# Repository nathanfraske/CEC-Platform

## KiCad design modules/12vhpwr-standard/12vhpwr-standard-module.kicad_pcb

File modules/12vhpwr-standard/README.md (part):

# 12VHPWR Standard module

Standard-tier **per-pin** sensing module for the **12VHPWR / 12V‑2×6** (PCIe CEM
5.x, 600 W GPU) connector. BOM target **$49** (100-qty). See spec
[§6.1](../../CEC-Platform-Ground-Truth-Spec.md).

Per CLAUDE.md's 2026-07-03 alpha/beta convention: this board is the **ALPHA**
line (validated, fab-snapshotted prototype); refinements land as **BETA**
revisions per the standard-tier beta plan
(`docs/standard-tier-review/SYNTHESIS-beta-plan.md`).

| Item | Decision |
|---|---|
| Tier | Standard |
| MCU | ESP32-S3-MINI-1-N4R2 (locked; same MINI-1 as the other modules) |
| Hub link | RJ-45 8P8C **shielded FTP**, locking boot (J1) — Kinghelm **KH-RJ45-58-8P8C** (LCSC **C2683360**), the same already-sourced jack as the Hub (§2.1; 2026-06-06). Drop-in on the routed 1.27 mm land (pads 1–8 identical to the old 54602). |
| Power connector | **12V‑2×6** (Molex Micro‑Fit+ / Amphenol Minitek, 16‑ckt: 6×+12V, 6×GND, 4 sideband). **J3 = board-mount right‑angle MALE header** (the PSU 12V‑2×6 cable plugs in). **J4 = captive OUTPUT pigtail** (a 12V‑2×6 cable soldered to the board, female plug → GPU). There is **no stock board‑mount female** 12V‑2×6 (it only exists as a cable plug), so this male‑in / soldered‑pigtail‑out is the minimal‑mated‑pair inline form (§2.8). |
| Sensing | **Per-pin**: six **INA240** current-sense amps, one across each +12V pin's **1 mΩ** shunt (RS1–6), feeding the ESP32-S3 ADC (IO1–6) directly — **no I²C sensing bus**. REF1/REF2 → GND (unidirectional forward). A **47k/10k divider** (R5/R6, **0.1%**) brings the rail voltage into a 7th ADC channel. With the **REF3030 ratiometric reference** (U4, v3.8) accuracy is **~±0.3–0.5%** on V and all six I (see **OQ-8** + the Voltage-ref row). |
| Input filter | Per-channel **anti-alias / transient RC** on each INA240 input: matched **10 Ω** series Rf on IN+/IN− (RFH1–6 / RFL1–6) + a **470 nF** differential cap (CF1–6). **fc = 1/(2π·2·Rf·Cdiff) ≈ 16.9 kHz**, so the ~10 kHz GPU transients this pass targets pass at ~−1.3 dB and HF is rolled off ahead of the ADC. Rf held at 10 Ω + matched (TI's INA240 ceiling) → negligible gain/CMRR error. *(Optional ~47 nF common-mode caps deferred — OQ-8.)* |
| Sideband | The four **12V-2×6 sense pins** (13–16: SENSE0, SENSE1, CARD_PWR_STABLE, CARD_CBL_PRES#) pass straight through J3→J4 **and** each taps a free ESP32-S3 GPIO (IO8/9/11/12) via a **1 kΩ** series R (R10–R13), so firmware can read the cable's advertised power capability + present/stable state and report it over CAN. |
| Temperature *(v3.7)* | **2× NTC 10k** (Murata **NCP15XH103F03RC** / LCSC **C77131**, 0402) into spare ESP32-S3 **ADC2** channels (this module never uses Wi-Fi, so ADC2 is free): **TH1** in the **12V power section by the shunt row** (board/shunt temperature), **TH2** ambient at a cool edge. Each is an NTC / 10 kΩ (R20/R21) / 100 nF (C20/C21) divider → **IO13 / IO14**; firmware reports temperature and **ΔT above ambient**. Purpose is **measurement quality + board health**: compensate the shunt-TCR / INA240-gain drift on the per-pin current readings, and flag 12V-section overheating — then board temp + per-pin current + rail voltage **fuse** to infer the off-board GPU-side condition. **Board-only**; a pigtail/GPU-plug NTC (the direct GPU-contact read) is **deferred**. Spec [§6.1](../../CEC-Platform-Ground-Truth-Spec.md). |
| Voltage ref *(v3.8)* | **REF3030** (U4, 3.0 V, SOT-23) measured on **ADC1 IO8** for **ratiometric correction** — firmware ratios out the ESP-ADC gain/reference drift, lifting the rail divider **and** all six current channels from ~±1% to **~±0.3–0.5%** (with **0.1%** R5/R6). Bypass C22 (OUT) + C23 (IN). The deliberate **middle ground** below the Pro's LTC2358-18; the REF3030 (3.0 V) is *measured* by the ADC, unlike the Pro's REF3033 (3.3 V) which feeds the LTC2358 ref. IO8 was freed by moving the SENSE0 sideband tap → **IO15**. See **OQ-8**. |
| Streaming | RS-485 **not populated** (Standard); pair 2 terminated module-side |
| DETECT | 2.2 kΩ precision (R1) — CAN-only code (§2.3, OQ-6 resolved); poke-and-ack tap R7 → IO10 (OQ-28) |
| Protection | No per-pin PoE/over-voltage (Standard/Pro, §2.4 v2.0); low-cap ESD diode **D1 = PESD5V0S1BA** (SOD-323, LCSC **C5261083**) on DETECT pin 8 — corrected from the non-SOD-323 PESD5V0S1UL on the 2026-06-06 sourcing pass |
| Flash/debug | USB-C (J5) on the ESP32-S3 native USB + BOOT/RESET buttons (SW1/SW2); VBUS ORs into +5VSB via D2 (SS34); CC1/CC2 = 5.1 kΩ |
| BOM target | $49 (100-qty) |

> ✅ **12V‑2×6 footprint LOCKED (2026-06-05).** `lib/cec.pretty/CEC_12V2x6_Horizontal`
> is now the **official Molex footprint** — Molex **219116** PCIe CEM5 12V‑2×6
> right‑angle THT header, MPN **2191161161** (T&R) = **2191160161** (tray), doc
> 2191160001‑SD — vendored from Molex's KiCad export, pads remapped to the schematic
> numbering: **1–6 = +12V** (row adjacent to the signal pins), **7–12 = GND** (outer
> row), **13–16 = sideband S1–S4**. Real geometry: 3 mm pitch, power drill 1.07 mm /
> 1.52 mm pad, signal drill 0.61 mm / 1.14 mm pad; **9.2 A/power pin**, 12 V.
>
> Two follow‑ups: **(1) safety —** the connector is symmetric (both rows are just
> "POWER"); +12V vs GND is the system/CEM assignment, so **verify pins 7–12 = GND**
> (i.e. 1–6 = +12V) against PCIe CEM5.1 / the target GPU before powering, since the
> schematic ties 7–12 to the GND plane. **(2) board pickup —** the board still
> carries the old approximate land; in KiCad do **Update Footprints from Library**
> to pull this one (converts + remaps nets by pad number), then orient **J3 rot 180
> / J4 rot 0** (this footprint's mouth is on +y, so that puts the mouth out the edge
> with GND toward the shunts). The real ~1.5 mm pad gaps let the +12V lanes neck
> between the GND barrels (vs the old ~0.6 mm approximate that trapped them).

## Open questions touching this board

- **OQ-8 (RESOLVED, v3.8 — revises the v3.7 no-ref call):** rail accuracy — a
  **REF3030** (3.0 V) ratiometric reference (U4), measured by the ESP ADC1, lifts
  the rail divider **and** all six current channels from ~±1% to **~±0.3–0.5%**
  (0.1% R5/R6) — the **middle ground** between the bare divider and the Pro's
  precision instrument. It's the *reference*, not a second ADC or a sensing bus, so
  Standard stays the fast firehose, just accurate + stable (stability is what makes
  a connector-degradation / dV·dI source-impedance trend real). Full simultaneous
  precision stays the Pro (LTC2358-18 + REF3033). Note: Standard REF3030 = 3.0 V
  (*measured* by the ADC); Pro REF3033 = 3.3 V (feeds the LTC2358 ref).
- *(OQ-11 resolved 2026-07-02 — per-pin shunt part (1 mΩ, §6.4) LOCKED to Bourns
  CSS2H-2512R-1L00F, already the sourced part on this board.)*
- *(OQ-6 module-ID encoding resolved — CAN-only = 2.2 kΩ.)*

## High-current 12V routing — fanned per-pin lanes

See **`12vhpwr-routing-plan.png`** (regenerate with
`scripts/gen-hpwr-routing-plan.py`) — it carries the full to-placement top-down,
the four-wire Kelvin detail, the 4-layer stackup, and the width/via/stitch tables.
The 6×+12V pins carry ~**8.3 A each** (600 W ÷ 12 V = 50 A); **uneven sharing is
what melts these connectors**, so the module gives each pin its own 1 mΩ shunt +
INA240 and keeps the six 12V lanes symmetric so it adds no imbalance (and detects
any). Routing spec (laid in the GUI — the generator only sets placement):

- **Lanes / fan-out:** J3 and J4 are 12V‑2×6 connectors with a fixed **3 mm pin
  pitch**, centered on the power section; the six +12V lanes **fan out symmetrically
  to a ~6 mm SENSE pitch**, so each lane gets its OWN column — in-line shunt → RC
  filter → INA240 stacked straight down (no staggering, short in-column Kelvin) —
  then **fan back in** to J4. **J4 is placed rot 180°** (mouth out the bottom edge =
  correct OUT orientation, mirroring J3 at the top); since the six +12V pins are
  electrically interchangeable (all common to the GPU 12V plane, current already
  measured at each shunt upstream), each lane's load side is mapped to the J4 +12V
  pad directly below it (pin 6−*j*) so the lanes still **don't cross** despite the
  180. The symmetric fan keeps the lanes in equal-length pairs; if the small inner/outer
  length spread matters, length-match the straight section in the GUI (the 1 mΩ
  shunt + connector-contact R dominate, so it's minor).
- **Width (IPC-2221, 2 oz outer):** design to the **contact** rating, not nominal —
  Micro-Fit+ ≈ 9.5–13.5 A/contact → **13 A/pin**. Route each lane **2.5 mm on F.Cu,
  mirrored 2.5 mm on B.Cu, paralleled** (≈13 A at <10 °C rise; ≥3.0 mm if a B.Cu
  mirror is interrupted). **12V on both 2 oz outers; GND solid on In1 + In2** (1 oz,
  set BOTH inner pours to GND). Stack is **12V / GND / GND / 12V**, so it's the GND
  pair that sits in the middle (sandwiched by the two 12V outers); each 12V lane
  runs **directly against a GND plane** (F.Cu over In1, B.Cu under In2) → its return
  image-current flows in that plane right beneath the lane → small loop area, low
  inductance. GND return = poured plane (never neck it).
- **Vias:** all current-carrying vias **0.5 mm drill / 0.9 mm pad (~2 A @10 °C,
  ~3 A @20 °C)**. Stitch F.Cu↔B.Cu **every ~5 mm down each lane**, with a **field of
  5–6** at every shunt terminal and **3–6 around each J3/J4 through-hole power pin**.
  Tie In1/In2/outer-GND on a **~5 mm grid** (denser ~3 mm ring at the connectors).
  Signal/sense vias 0.3/0.6 mm (~1 A) — avoid them on the Kelvin pair.
- **Kelvin sense (§6.8):** INA240A3 (gain 100) → 1 mΩ × 8.3 A × 100 = 0.83 V
  (13 A → 1.3 V). **Sense taps off the INNER shunt-terminal edges** (excludes pad/
  solder/trace IR drop); force current on the OUTER ends. The pair carries ~no
  current → run it **thin (0.20–0.25 mm)** as a **tight matched-length pair over the
  In1 GND plane**, kept off / perpendicular to the 12V lanes, with the RC input
  filter (RFH/RFL 10 Ω + CF 470 nF) placed **at the INA pins**. A GND guard-via
  fence alongside the pair is cheap insurance (the 12V here is essentially DC, so
  coupling is low, but the signal is only 8–13 mV).

## Status

Schematic generated by `scripts/gen-modules.py`; the initial PCB floorplan by
`scripts/gen-module-pcb.py` (one-shot — hand-maintained in the GUI afterwards):
4-layer, **2 oz outer / 1 oz inner**, **~58 × 80 mm** — the 12V‑2×6 power path runs
TOP→BOTTOM down the centre-left (J3 IN top → 6 **fanned** per-pin lanes, each with
its in-line shunt → RC filter → INA240 → bypass → J4 pigtail OUT bottom); the
ESP + CAN + LDO + flash front end + RJ-45/USB-C fill the RIGHT. The six +12V lanes
**fan out from J3/J4's 3 mm pin pitch to a ~6 mm sense pitch** so each lane gets its
own column (in-column shunt/filter/INA, short Kelvin, no staggering). The **plug
connectors overhang their board edge** so a cable seats without the board fouling
the plug overmold while the solder pads stay on-board: **J3** (PSU 12V‑2×6 IN, top-
centre) overhangs the **top** edge ~3 mm; **J1** (RJ-45) and **J5** (USB-C) overhang
the **right** edge. **J4** (12V‑2×6 OUT) is **rot 180°** so its mouth/body overhang
the **bottom** edge too (correct OUT orientation, mirroring J3); the +12V load nets
are remapped to the reversed pins (pin 6−*j*, interchangeable) so the lanes stay
non-crossing. It's a captive soldered pigtail (wires exit the bottom). **Three M3 corner mounts**
(TL/TR/BL) — the RJ-45's big jack body fills the bottom-right corner, and the three
through-hole connectors anchor that side. The **per-lane sense passives are now
placed** (RFH/RFL/CF input filter + the INA bypass C10–C15); **component values are
on F.SilkS**. **DRAFT** marker present; DRC is **clean of structural hits** (0 copper
shorts / clearance / courtyard / copper-edge) — the remaining silk-overlap warnings
are the dense values-on-silk + tight placement, a GUI silk-refinement task. Next in
GUI: *Update PCB from Schematic* to pull the remaining **control-side decoupling**
(C1–C8, R1/R2/R7, D1), then route + pour (§6.8 Kelvin, §6.7 high-current).
Project-local library tables point at `../../lib` via `${KIPRJMOD}`.

## Routing status (2026-06-05)

**Part audit — all clear.** Every vendored symbol used on this board (and in the
shared lib) had its pin#→name mapping checked against the manufacturer datasheet:
INA240 (1=IN−, 2=GND, 3=REF2, 4=NC → tied to GND, which the datasheet sanctions,
5=OUT, 6=V+, 7=REF1, 8=IN+), INA226/228/238 (identical DGS VSSOP‑10), TJA1051T/3,
LP5907, ESP32‑S3‑MINI‑1, RJ‑45, USB‑C, the 12V‑2×6, and the rest — **all correct,
no mis‑wires.** (Cosmetic‑only notes are in the repo CLAUDE.md.)

**High‑current path — DONE.** All six +12V lanes carry end‑to‑end: J3 +12V → shunt
on **F.Cu** (2.5 mm, fanned 3→6 mm), shunt → J4 +12V on **B.Cu** (2.5 mm). Lane 3's
full sense chain is routed as the reference.

**Remaining — 47 ratlines, all sense/signal** (see **`12vhpwr-route-plan.png`**,
regenerate with `scripts/gen-hpwr-route-status.py`):
- All six **INA OUT → ESP ADC IO1–6** (ISENSEP1–6).
- **Kelvin taps** off the inner shunt‑terminal edges → RFH/RFL, and **RC filter →
  INA IN+/IN−**, on lanes 1, 2, 4, 5, 6 (route them like the finished lane 3):
  0.25 mm matched pair over the In1 GND plane, ⊥ to the 12V lanes, filter at the INA.

**Before re‑checking DRC** (current DRC = 47 unconnected + 291 violations):
- **Fill All Zones (B).** 252 of the violations are `clearance`/`hole_clearance`
  reading *actual 0.000 mm* — that is **stale GND‑pour** (kicad‑cli cannot refill),
  not real shorts. Set **both** inner zones to GND.
- Delete **18 dangling vias + 3 dangling track stubs**.
- **Update PCB from Schematic** — syncs U2 value (the PCB still shows the old
  *TJA1462A*; the schematic is already *TJA1051T/3*, C38695; footprint identical).
- **Outline fixed:** the Molex 12V‑2×6 footprint's mouth/latch profile was on
  Edge.Cuts (read as a malformed board outline); moved to Dwgs.User in the library
  and in J3/J4 (invalid_outline 4→0).

**Note — J4 orientation:** with the official Molex footprint J4 is **rot 0°** (mouth
out the bottom edge) and J3 is **rot 180°** (mouth out the top); this supersedes the
"J4 rot 180°" wording in the Status paragraph above.

## BOM / JLC sourcing (2026-06-06)

Every component is sourced to an LCSC part (written into the schematic symbol
`LCSC`/`MPN`/`Manufacturer` props) and exported in `bom/`:
`bom.csv` (tracking) + `12vhpwr-standard-BOM-jlcpcb.csv` (Comment/Designator/Footprint/LCSC).
**~$21/board** in JLCPCB parts (single-qty pricing) + the consigned Molex 12V‑2×6 —
comfortably under the **$49** target; cost is dominated by **6× INA240A3DR ($1.87 ea =
$11.24)**, the **ESP32 ($4.59)**, and the **6× 1 mΩ shunts ($0.52 ea)**.

Pinouts datasheet-verified this pass (INA240 SBOS662C, LP5907 SNVS798Q, ESP32‑S3‑MINI‑1
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
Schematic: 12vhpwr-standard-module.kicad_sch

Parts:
C1, C2: 1uF; C_0603_1608Metric; MPN CL10B105KA8NNNC; LCSC C29936
C3, C4, C5, C8, C10, C11, C12, C13, C14, C15, C20, C21, C22, C23: 100nF; C_0402_1005Metric; MPN CL05B104KO5NNNC; LCSC C1525
C6, C7, C9: 10uF; C_0805_2012Metric; MPN CL21A106KAYNNNE; LCSC C15850
C24: 1nF; C_0402_1005Metric; MPN GRM1555C1H102JA01D; LCSC C76947
CF1, CF2, CF3, CF4, CF5, CF6: 470nF; C_0603_1608Metric; MPN CL10B474KA8NNNC; LCSC C1623
D1: PESD5V0S1BA; D_SOD-323; MPN PESD5V0S1BA; LCSC C5261083
D2: SS34; D_SMA; MPN SS34; LCSC C8678
J1: TO-HUB; RJ45_FTP_Shielded_Horizontal; MPN KH-RJ45-58-8P8C; LCSC C2683360
J3: 12V-2x6 IN; CEC_12V2x6_Horizontal; MPN 2191161161; JLCPCB consigned (not in JLC catalog)
J4: 12V-2x6 OUT pigtail; CEC_12V2x6_Horizontal; MPN 2191161161; JLCPCB consigned (not in JLC catalog)
J5: USB-C 2.0; USB_C_Receptacle_XKB_U262-16XN-4BVC11; MPN U262-161N-4BVC11; LCSC C319148
R1: 2.2kΩ; R_0402_1005Metric; MPN 0402WGF2201TCE; LCSC C25879
R2, R20, R21: 10kΩ; R_0402_1005Metric; MPN 0402WGF1002TCE; LCSC C25744
R5: 47kΩ; R_0402_1005Metric; Tolerance 0.1%; MPN RT0402BRD0747KL; LCSC C728561
R6: 10kΩ; R_0402_1005Metric; Tolerance 0.1%; MPN RT0402BRD0710KL; LCSC C190095
R7: 100kΩ; R_0402_1005Metric; MPN 0402WGF1003TCE; LCSC C25741
R8, R9: 5.1kΩ; R_0402_1005Metric; MPN 0402WGF5101TCE; LCSC C25905
R10, R11, R12, R13: 1kΩ; R_0402_1005Metric; MPN 0402WGF1001TCE; LCSC C11702
RFH1, RFH2, RFH3, RFH4, RFH5, RFH6: 10Ω; R_0402_1005Metric; Tolerance 0.1%; MPN RT0402BRE0710RL; LCSC C705642
RFL1, RFL2, RFL3, RFL4, RFL5, RFL6: 10Ω; R_0402_1005Metric; Tolerance 0.1%; MPN RT0402BRE0710RL; LCSC C705642
RS1, RS2, RS3, RS4, RS5, RS6: 1mΩ; R_2512_6332Metric; MPN CSS2H-2512R-1L00F; LCSC C4175647
SW1: BOOT; TS-1088-AR02016; MPN TS-1088-AR02016; LCSC C720477
SW2: RESET; TS-1088-AR02016; MPN TS-1088-AR02016; LCSC C720477
TH1, TH2: NTC 10k; NTC_0402_1005Metric; MPN NCP15XH103F03RC; LCSC C77131
U1: ESP32-S3-MINI-1-N4R2; ESP32-S2-MINI-1_NoAntKeepout; MPN ESP32-S3-MINI-1-N4R2; LCSC C3013941
U2: TJA1051T/3; SOIC-8_3.9x4.9mm_P1.27mm; MPN TJA1051T/3; LCSC C38695
U3: LP5907MFX-3.3; SOT-23-5; MPN LP5907MFX-3.3; LCSC C80670
U4: REF3030; REF3030_DBZ3; MPN REF3030AIDBZR; LCSC C38423
U10, U11, U12, U13, U14, U15: INA240A3; SOIC-8_3.9x4.9mm_P1.27mm; MPN INA240A3DR; LCSC C2060584

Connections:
+3V3: C2.1, C3.1, C7.1, C8.1, C10.1, C11.1, C12.1, C13.1, C14.1, C15.1, C23.1, R2.1, TH1.1, TH2.1, U1.3 (3V3), U2.5 (VIO), U3.5 (OUT), U4.1 (IN), U10.6 (V+), U11.6 (V+), U12.6 (V+), U13.6 (V+), U14.6 (V+), U15.6 (V+)
+5VSB: C1.1, C4.1, C6.1, D2.1 (K), J1.1 (VCC), U2.3 (VCC), U3.1 (IN), U3.3 (EN)
/CAN_H: J1.3 (CAN1_H), U2.7 (CANH)
/CAN_L: J1.6 (CAN1_L), U2.6 (CANL)
/CAN_RX: U1.22 (IO18), U2.4 (RXD)
/CAN_TX: U1.21 (IO17), U2.1 (TXD)
/DETECT: D1.1 (K), J1.8 (DETECT), R1.1, R7.1
/DETECT_SENSE: R7.2, U1.14 (IO10)
/EN: C5.1, R2.2, SW2.2, U1.45 (EN)
/GPIO0: SW1.2, U1.4 (IO0)
/IN1_N: CF1.2, RFL1.2, U10.1 (-)
/IN1_P: CF1.1, RFH1.2, U10.8 (+)
/IN2_N: CF2.2, RFL2.2, U11.1 (-)
/IN2_P: CF2.1, RFH2.2, U11.8 (+)
/IN3_N: CF3.2, RFL3.2, U12.1 (-)
/IN3_P: CF3.1, RFH3.2, U12.8 (+)
/IN4_N: CF4.2, RFL4.2, U13.1 (-)
/IN4_P: CF4.1, RFH4.2, U13.8 (+)
/IN5_N: CF5.2, RFL5.2, U14.1 (-)
/IN5_P: CF5.1, RFH5.2, U14.8 (+)
/IN6_N: CF6.2, RFL6.2, U15.1 (-)
/IN6_P: CF6.1, RFH6.2, U15.8 (+)
/ISENSEP1: U1.5 (IO1), U10.5
/ISENSEP2: U1.6 (IO2), U11.5
/ISENSEP3: U1.7 (IO3), U12.5
/ISENSEP4: U1.8 (IO4), U13.5
/ISENSEP5: U1.9 (IO5), U14.5
/ISENSEP6: U1.10 (IO6), U15.5
/SB_CBL_PRES: J3.16 (SENSE), J4.16 (SENSE), R13.1
/SB_CBL_PRES_GPIO: R13.2, U1.16 (IO12)
/SB_PWR_STABLE: J3.15 (SENSE), J4.15 (SENSE), R12.1
/SB_PWR_STABLE_GPIO: R12.2, U1.15 (IO11)
/SB_SENSE0: J3.13 (SENSE), J4.13 (SENSE), R10.1
/SB_SENSE0_GPIO: R10.2, U1.19 (IO15)
/SB_SENSE1: J3.14 (SENSE), J4.14 (SENSE), R11.1
/SB_SENSE1_GPIO: R11.2, U1.13 (IO9)
/SENSEP1_HI: J3.1 (+12V), RFH1.1, RS1.1
/SENSEP1_LO: J4.6 (+12V), RFL1.1, RS1.2
/SENSEP2_HI: J3.2 (+12V), RFH2.1, RS2.1
/SENSEP2_LO: J4.5 (+12V), RFL2.1, RS2.2
/SENSEP3_HI: J3.3 (+12V), RFH3.1, RS3.1
/SENSEP3_LO: J4.4 (+12V), RFL3.1, RS3.2
/SENSEP4_HI: J3.4 (+12V), RFH4.1, RS4.1
/SENSEP4_LO: J4.3 (+12V), RFL4.1, RS4.2
/SENSEP5_HI: J3.5 (+12V), RFH5.1, RS5.1
/SENSEP5_LO: J4.2 (+12V), RFL5.1, RS5.2
/SENSEP6_HI: J3.6 (+12V), R5.1, RFH6.1, RS6.1
/SENSEP6_LO: J4.1 (+12V), RFL6.1, RS6.2
/TEMP1: C20.1, R20.1, TH1.2, U1.17 (IO13)
/TEMP2: C21.1, R21.1, TH2.2, U1.18 (IO14)
/USB_CC1: J5.A5 (CC1), R8.1
/USB_CC2: J5.B5 (CC2), R9.1
/USB_DM: J5.A7 (D-), J5.B7 (D-), U1.23 (USB_D-)
/USB_DP: J5.A6 (D+), J5.B6 (D+), U1.24 (USB_D+)
/VBUS: C9.1, D2.2 (A), J5.A4 (VBUS), J5.A9 (VBUS), J5.B4 (VBUS), J5.B9 (VBUS)
/VRAIL_DIV: C24.1, R5.2, R6.1, U1.11 (IO7)
/VREF: C22.1, U1.12 (IO8), U4.2 (OUT)
GND: C1.2, C2.2, C3.2, C4.2, C5.2, C6.2, C7.2, C8.2, C9.2, C10.2, C11.2, C12.2, C13.2, C14.2, C15.2, C20.2, C21.2, C22.2, C23.2, C24.2, D1.2 (A), J1.2 (GND), J1.SH1 (SHIELD), J1.SH2 (SHIELD), J3.7 (GND), J3.8 (GND), J3.9 (GND), J3.10 (GND), J3.11 (GND), J3.12 (GND), J4.7 (GND), J4.8 (GND), J4.9 (GND), J4.10 (GND), J4.11 (GND), J4.12 (GND), J5.A1 (GND), J5.A12 (GND), J5.B1 (GND), J5.B12 (GND), J5.S1 (SHIELD), R1.2, R6.2, R8.2, R9.2, R20.2, R21.2, SW1.1, SW2.1, U1.1 (GND), U1.2 (GND), U1.42 (GND), U1.43 (GND), U1.46 (GND), U1.47 (GND), U1.48 (GND), U1.49 (GND), U1.50 (GND), U1.51 (GND), U1.52 (GND), U1.53 (GND), U1.54 (GND), U1.55 (GND), U1.56 (GND), U1.57 (GND), U1.58 (GND), U1.59 (GND), U1.60 (GND), U1.61 (GND), U1.62 (GND), U1.63 (GND), U1.64 (GND), U1.65 (GND), U2.2 (GND), U2.8 (S), U3.2 (GND), U4.3 (GND), U10.2 (GND), U10.3 (REF2), U10.4 (GND), U10.7 (REF1), U11.2 (GND), U11.3 (REF2), U11.4 (GND), U11.7 (REF1), U12.2 (GND), U12.3 (REF2), U12.4 (GND), U12.7 (REF1), U13.2 (GND), U13.3 (REF2), U13.4 (GND), U13.7 (REF1), U14.2 (GND), U14.3 (REF2), U14.4 (GND), U14.7 (REF1), U15.2 (GND), U15.3 (REF2), U15.4 (GND), U15.7 (REF1); also elsewhere on the board

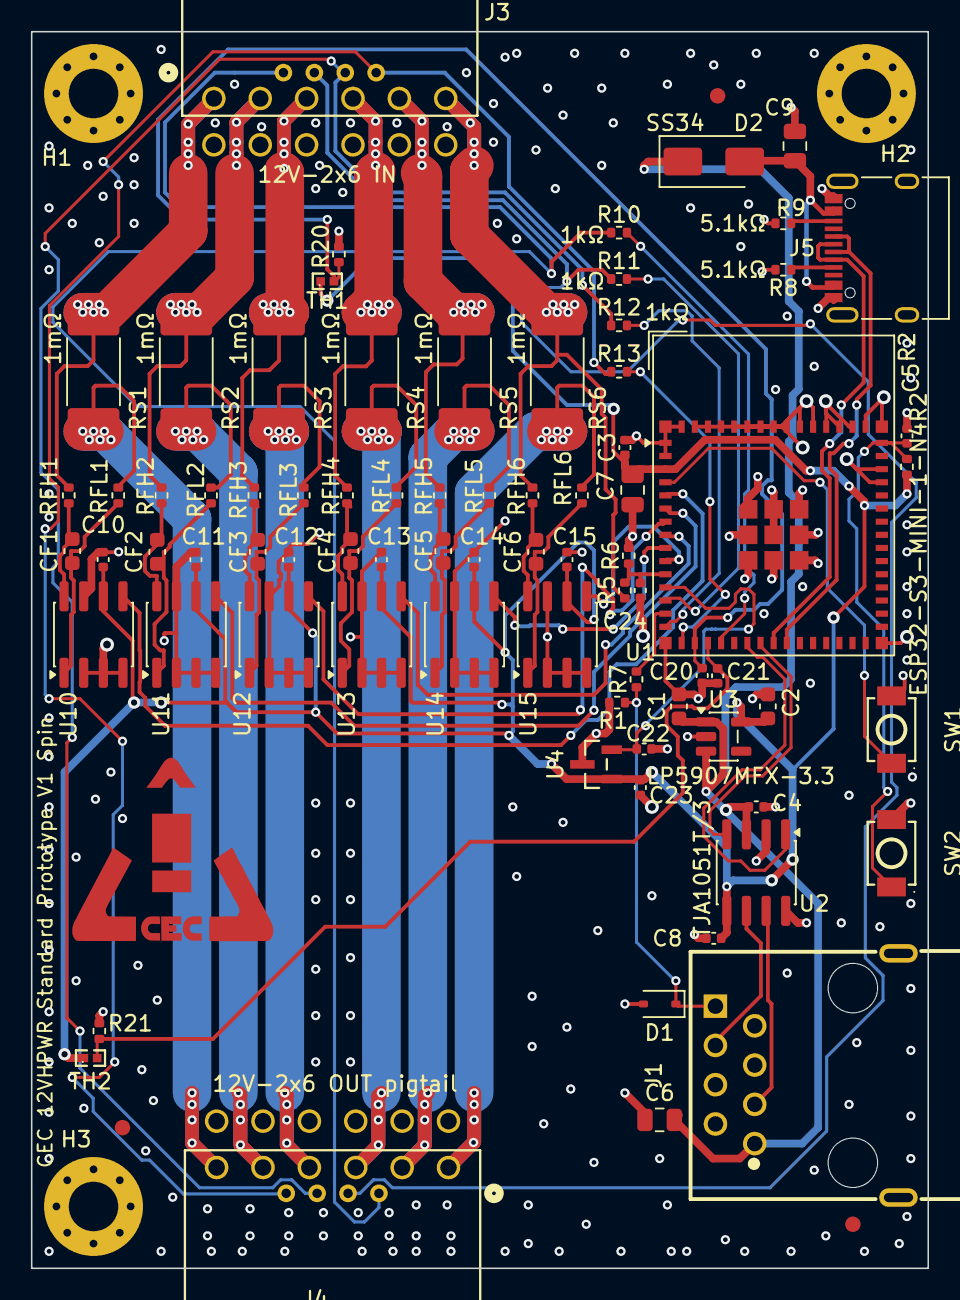
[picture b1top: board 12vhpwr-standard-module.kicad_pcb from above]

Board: 4 copper layers, 58.0 x 80.0 mm, 84 parts (0 on the bottom side), 58 nets.

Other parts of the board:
FID1, FID2, FID3: Fiducial_1mm_Mask2mm
H1, H2, H3: MountingHole_3.2mm_M3_Pad_Via
LOGO1: CEC_Logo_Copper

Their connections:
GND: H1.1, H2.1, H3.1; also elsewhere on the board

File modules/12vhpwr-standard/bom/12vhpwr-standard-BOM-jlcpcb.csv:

Comment,Designator,Footprint,LCSC
1uF,"C1,C2",C_0603_1608Metric,C29936
100nF,"C3,C4,C5,C8,C10,C11,C12,C13,C14,C15,C20,C21,C22,C23",C_0402_1005Metric,C1525
10uF,"C6,C7,C9",C_0805_2012Metric,C15850
1nF,C24,C_0402_1005Metric,C76947
470nF,"CF1,CF2,CF3,CF4,CF5,CF6",C_0603_1608Metric,C1623
PESD5V0S1BA,D1,D_SOD-323,C5261083
SS34,D2,D_SMA,C8678
TO-HUB,J1,RJ45_FTP_Shielded_Horizontal,C2683360
12V-2x6 IN,J3,CEC_12V2x6_Horizontal,
12V-2x6 OUT pigtail,J4,CEC_12V2x6_Horizontal,
USB-C 2.0,J5,USB_C_Receptacle_XKB_U262-16XN-4BVC11,C319148
2.2kΩ,R1,R_0402_1005Metric,C25879
10kΩ,"R2,R20,R21",R_0402_1005Metric,C25744
47kΩ,R5,R_0402_1005Metric,C728561
10kΩ,R6,R_0402_1005Metric,C190095
100kΩ,R7,R_0402_1005Metric,C25741
5.1kΩ,"R8,R9",R_0402_1005Metric,C25905
1kΩ,"R10,R11,R12,R13",R_0402_1005Metric,C11702
10Ω,"RFH1,RFH2,RFH3,RFH4,RFH5,RFH6,RFL1,RFL2,RFL3,RFL4,RFL5,RFL6",R_0402_1005Metric,C705642
1mΩ,"RS1,RS2,RS3,RS4,RS5,RS6",R_2512_6332Metric,C4175647
BOOT,SW1,TS-1088-AR02016,C720477
RESET,SW2,TS-1088-AR02016,C720477
NTC 10k,"TH1,TH2",NTC_0402_1005Metric,C77131
ESP32-S3-MINI-1-N4R2,U1,ESP32-S2-MINI-1_NoAntKeepout,C3013941
TJA1051T/3,U2,SOIC-8_3.9x4.9mm_P1.27mm,C38695
LP5907MFX-3.3,U3,SOT-23-5,C80670
REF3030,U4,REF3030_DBZ3,C38423
INA240A3,"U10,U11,U12,U13,U14,U15",SOIC-8_3.9x4.9mm_P1.27mm,C2060584

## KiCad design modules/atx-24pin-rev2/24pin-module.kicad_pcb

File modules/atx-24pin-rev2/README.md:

# atx-24pin-rev2 — right-angle layout variant

Same circuit as [`../atx-24pin`](../atx-24pin) (the canonical 24-pin ATX
interposer); **different PCB layout only** — 24-pin input (J3) with the 24-pin
output (J4) rotated 90° CCW for a right-angle cable exit.

## Known issue (prototype run) — RJ-45 VCC parallels the JST feed

rev2 ties **J1 pin 1 (RJ-45 VCC)** to `+5VSB`, so the module feeds the Hub on
**both** the dedicated JST 5VSB feed **and** its RJ-45 VCC pin, in parallel.
Because the Hub power mux sits only in the JST leg (JST = mux input, RJ-45 VCC =
mux output), a **short RJ-45 patch** makes the RJ-45 the lower-resistance path —
it carries the majority of the bulk current (up to ~1.7 A at 3 A total, over the
**1.5 A RJ-45 contact rating**) and bypasses the mux's PSU/USB OR-ing. Fixed on
rev3 by leaving J1.1 open (spec §2.7 v3.3); rev2 is ordered as-is, so mitigate at
bring-up — any one of:

1. **Long RJ-45 patch (≥1.5–2 m)** on the 24-pin↔Hub link: the conductor
   resistance then exceeds the JST+mux path, so the JST carries the bulk. No mod.
2. **Keep total 5VSB low:** cap the firmware LED budget and don't run all ports
   full-white. Under ~2 A total, even a 50/50 split keeps the RJ-45 VCC well
   under 1.5 A.
3. **Bodge — open J1 pin 1:** lift the RJ-45 VCC pin or knife-cut its trace to
   `+5VSB`, emulating the rev3 fix. Most robust; do this if you'll push full
   load. The module still self-powers from its ATX tap.

Don't run a fully-populated, full-LED system through a short patch on an
un-bodged rev2.

## Shared schematic (canonical = atx-24pin)
The schematic here is a **synced copy**. The source of truth is
`../atx-24pin/24pin-module.kicad_sch`.

1. Edit the schematic in `../atx-24pin`.
2. Run `./sync-schematic.sh` here to refresh this copy.
3. **Tools → Update PCB from Schematic** in this project's board.

Do not edit this copy directly — `sync-schematic.sh` overwrites it from canonical.

## PCB
Starts as a blank slate: **only J3 and J4 are placed**, on the inherited 1 oz
stackup + netclasses (USB/CAN/Power/HighCurrent) + design rules. Everything else
arrives via *Update PCB from Schematic*, ready to place around the right-angle
header arrangement. (A fresh DRC will show unconnected items until that import.)

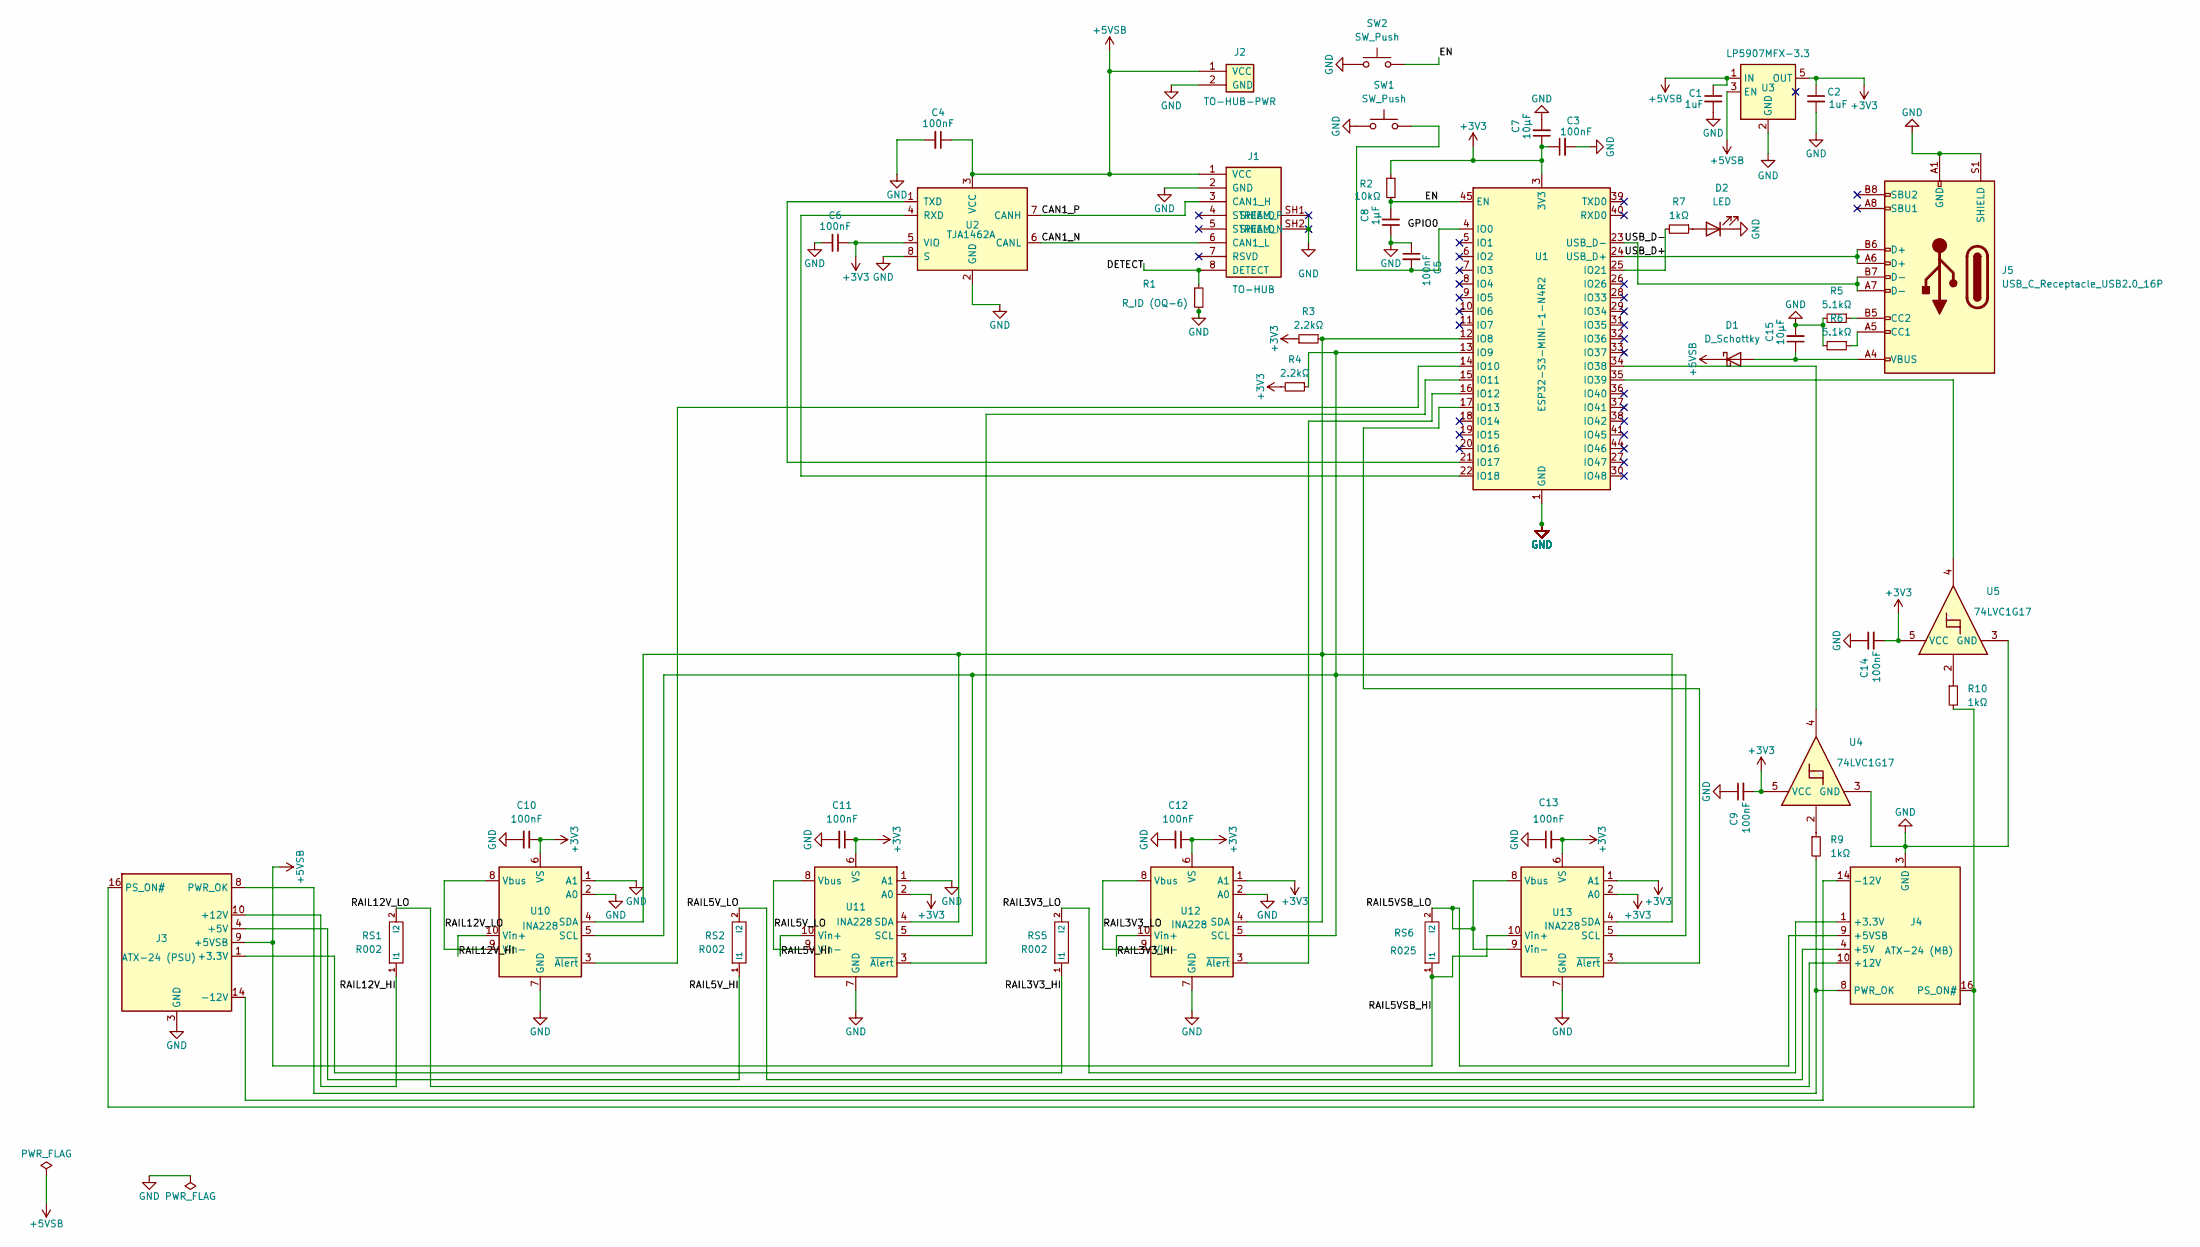
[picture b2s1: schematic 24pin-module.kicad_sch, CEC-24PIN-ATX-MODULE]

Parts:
C1, C2: 1uF; C_0603_1608Metric; Tolerance 10%; Voltage 25V
C3, C4, C5, C6, C10, C11, C12, C13: 100nF; C_0402_1005Metric; Tolerance 10%; Voltage 25V
C7, C15: 10µF; C_0805_2012Metric; Tolerance 10%; Voltage 25V
C8: 1µF; C_0805_2012Metric; Tolerance 10%; Voltage 25V
C9, C14: 100nF; C_0402_1005Metric; Voltage 25V; Tolerance 10%
D1: D_Schottky; D_SMA; MPN SS34; LCSC C8678
D2: LED; LED_0603_1608Metric
J1: TO-HUB; RJ45_Amphenol_54602-x08_Horizontal
J2: TO-HUB-PWR; JST_XH_S2B-XH-A_1x02_P2.50mm_Horizontal
J3: ATX-24 (PSU); Molex_Mini-Fit_Jr_5569-24A1_2x12_P4.20mm_Horizontal
J4: ATX-24 (MB); Molex_Mini-Fit_Jr_5569-24A1_2x12_P4.20mm_Horizontal
J5: USB_C_Receptacle_USB2.0_16P; USB_C_Receptacle_XKB_U262-16XN-4BVC11
R1: R_ID (OQ-6); R_0402_1005Metric; Tolerance 1%
R2: 10kΩ; R_0402_1005Metric; Tolerance 1%
R3, R4: 2.2kΩ; R_0402_1005Metric; Tolerance 1%
R5, R6: 5.1kΩ; R_0402_1005Metric; Tolerance 1%
R7, R9, R10: 1kΩ; R_0402_1005Metric; Tolerance 1%
RS1, RS2, RS5: R002; R_2512_6332Metric; Tolerance 1%; MPN CSS2H-2512K-2L00F; LCSC C1729157
RS6: R025; R_2512_6332Metric; Tolerance 1%
SW1, SW2: SW_Push; Panasonic_EVQPUJ_EVQPUA
U1: ESP32-S3-MINI-1-N4R2; ESP32-S2-MINI-1_NoAntKeepout; MPN ESP32-S3-MINI-1-N4R2; LCSC C3013941
U2: TJA1462A; SOIC-8_3.9x4.9mm_P1.27mm; MPN TJA1462AT/0Z; LCSC C3234095
U3: LP5907MFX-3.3; SOT-23-5; MPN LP5907MFX-3.3/NOPB; LCSC C80670
U4, U5: 74LVC1G17; SOT-23-5; MPN SN74LVC1G17DBVR; LCSC C7836
U10, U11, U12, U13: INA228; VSSOP-10_3x3mm_P0.5mm; MPN INA228AIDGSR; LCSC C2887910

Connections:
+3V3: C2.1, C3.1, C6.1, C7.1, C9.2, C10.1, C11.1, C12.1, C13.2, C14.2, R2.1, R3.1, R4.2, U1.3 (3V3), U2.5 (VIO), U3.5 (OUT), U4.5 (VCC), U5.5 (VCC), U10.6 (VS), U11.2 (A0), U11.6 (VS), U12.1 (A1), U12.6 (VS), U13.1 (A1), U13.2 (A0), U13.6 (VS)
+5VSB: C1.1, C4.1, D1.1 (K), J1.1 (VCC), J2.1 (VCC), J3.9 (+5VSB), RS6.1 (I1), U2.3 (VCC), U3.1 (IN), U3.3 (EN), U13.10 (Vin+)
/CAN1_N: J1.6 (CAN1_L), U2.6 (CANL)
/CAN1_P: J1.3 (CAN1_H), U2.7 (CANH)
/DETECT: J1.8 (DETECT), R1.1
/EN: C8.2, R2.2, SW2.2, U1.45 (EN)
/GPIO0: C5.2, SW1.2, U1.4 (IO0)
/RAIL3V3_HI: J3.1 (+3.3V), J3.2 (+3.3V), J3.12 (+3.3V), J3.13 (+3.3V), RS5.1 (I1), U12.10 (Vin+)
/RAIL3V3_LO: J4.1 (+3.3V), J4.2 (+3.3V), J4.12 (+3.3V), J4.13 (+3.3V), RS5.2 (I2), U12.8 (Vbus), U12.9 (Vin-)
/RAIL5VSB_LO: J4.9 (+5VSB), RS6.2 (I2), U13.8 (Vbus), U13.9 (Vin-)
/RAIL5V_HI: J3.4 (+5V), J3.6 (+5V), J3.21 (+5V), J3.22 (+5V), J3.23 (+5V), RS2.1 (I1), U11.10 (Vin+)
/RAIL5V_LO: J4.4 (+5V), J4.6 (+5V), J4.21 (+5V), J4.22 (+5V), J4.23 (+5V), RS2.2 (I2), U11.8 (Vbus), U11.9 (Vin-)
/RAIL12V_HI: J3.10 (+12V), J3.11 (+12V), RS1.1 (I1), U10.10 (Vin+)
/RAIL12V_LO: J4.10 (+12V), J4.11 (+12V), RS1.2 (I2), U10.8 (Vbus), U10.9 (Vin-)
/USB_D+: J5.A6 (D+), J5.B6 (D+), U1.24 (USB_D+)
/USB_D-: J5.A7 (D-), J5.B7 (D-), U1.23 (USB_D-)
GND: C1.2, C2.2, C3.2, C4.2, C5.1, C6.2, C7.2, C8.1, C9.1, C10.2, C11.2, C12.2, C13.1, C14.1, C15.2, D2.1 (K), J1.2 (GND), J1.SH1 (SHIELD), J1.SH2 (SHIELD), J2.2 (GND), J3.3 (GND), J3.5 (GND), J3.7 (GND), J3.15 (GND), J3.17 (GND), J3.18 (GND), J3.19 (GND), J3.24 (GND), J4.3 (GND), J4.5 (GND), J4.7 (GND), J4.15 (GND), J4.17 (GND), J4.18 (GND), J4.19 (GND), J4.24 (GND), J5.A1 (GND), J5.A12 (GND), J5.B1 (GND), J5.B12 (GND), J5.S1 (SHIELD), R1.2, R5.2, R6.2, SW1.1, SW2.1, U1.1 (GND), U1.2 (GND), U1.42 (GND), U1.43 (GND), U1.46 (GND), U1.47 (GND), U1.48 (GND), U1.49 (GND), U1.50 (GND), U1.51 (GND), U1.52 (GND), U1.53 (GND), U1.54 (GND), U1.55 (GND), U1.56 (GND), U1.57 (GND), U1.58 (GND), U1.59 (GND), U1.60 (GND), U1.61 (GND), U1.62 (GND), U1.63 (GND), U1.64 (GND), U1.65 (GND), U2.2 (GND), U2.8 (S), U3.2 (GND), U4.3 (GND), U5.3 (GND), U10.1 (A1), U10.2 (A0), U10.7 (GND), U11.1 (A1), U11.7 (GND), U12.2 (A0), U12.7 (GND), U13.7 (GND)
unnamed: C15.1, D1.2 (A), J5.A4 (VBUS), J5.A9 (VBUS), J5.B4 (VBUS), J5.B9 (VBUS)
unnamed: D2.2 (A), R7.1
unnamed: J3.14 (-12V), J4.14 (-12V)
unnamed: J3.16 (PS_ON#), J4.16 (PS_ON#), R10.2
unnamed: J3.8 (PWR_OK), J4.8 (PWR_OK), R9.2
unnamed: J5.A5 (CC1), R6.1
unnamed: J5.B5 (CC2), R5.1
unnamed: R9.1, U4.2
unnamed: R10.1, U5.2
unnamed: R3.2, U1.12 (IO8), U10.4 (SDA), U11.4 (SDA), U12.4 (SDA), U13.4 (SDA)
unnamed: R4.1, U1.13 (IO9), U10.5 (SCL), U11.5 (SCL), U12.5 (SCL), U13.5 (SCL)
unnamed: U1.14 (IO10), U10.3 (~Alert)
unnamed: U1.15 (IO11), U11.3 (~Alert)
unnamed: U1.16 (IO12), U12.3 (~Alert)
unnamed: U1.17 (IO13), U13.3 (~Alert)
unnamed: U1.21 (IO17), U2.1 (TXD)
unnamed: U1.22 (IO18), U2.4 (RXD)
unnamed: R7.2, U1.25 (IO21)
unnamed: U1.34 (IO38), U4.4
unnamed: U1.35 (IO39), U5.4

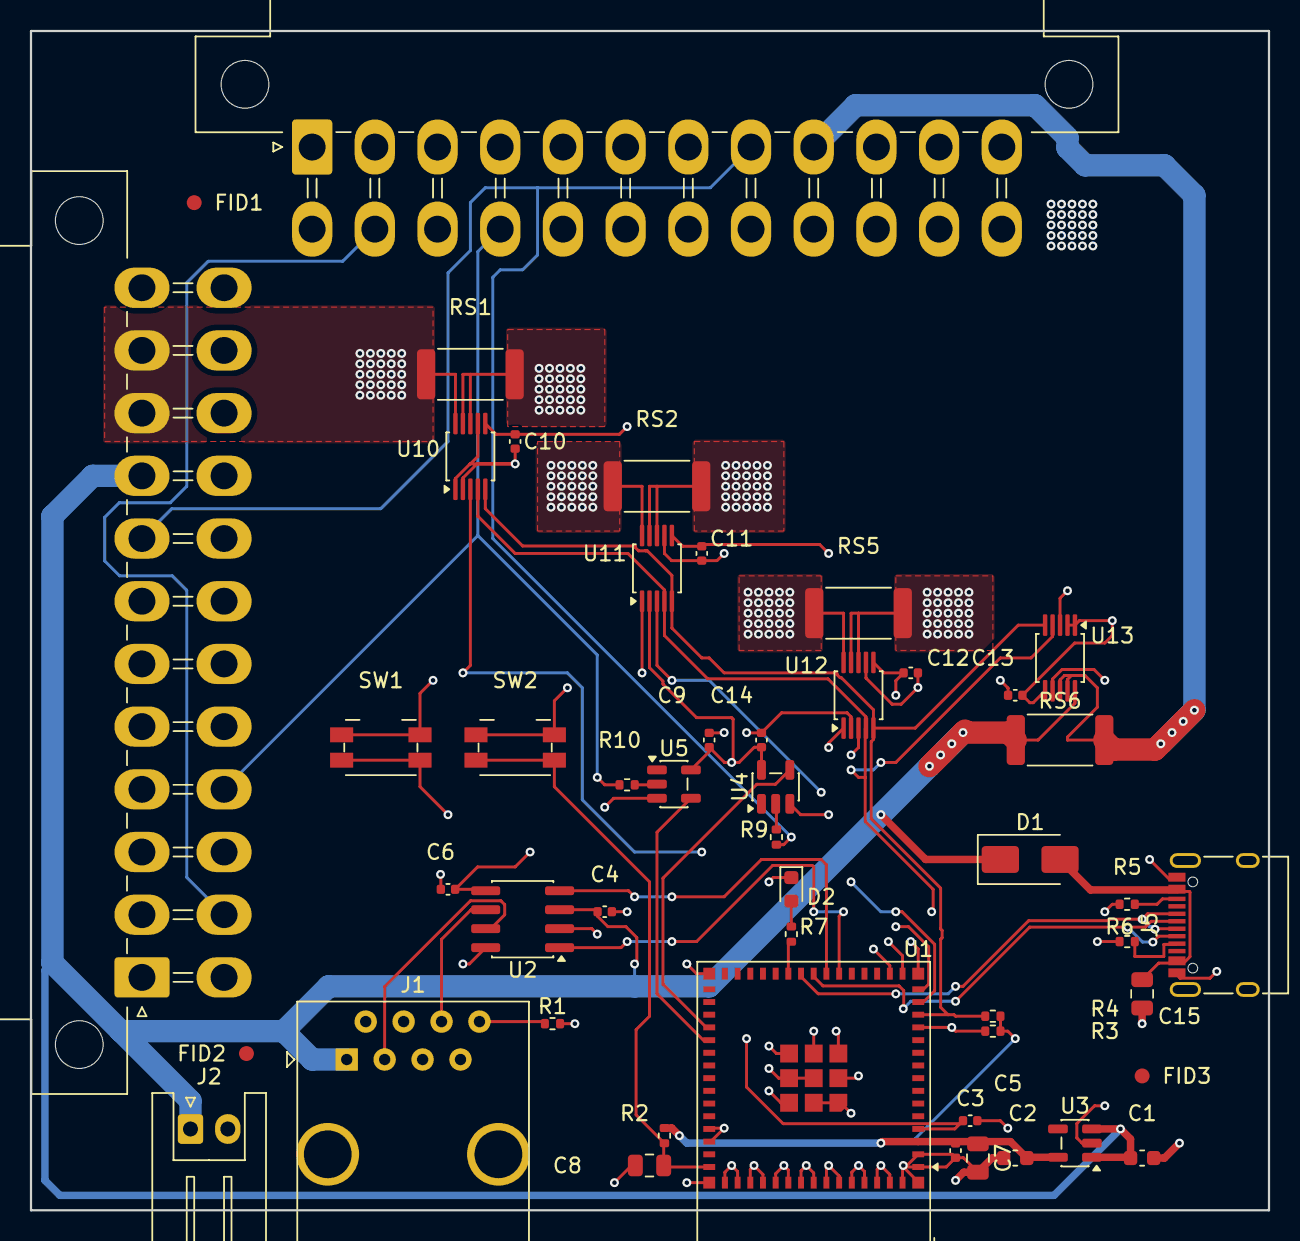
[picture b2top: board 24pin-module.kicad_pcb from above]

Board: 4 copper layers, 82.9 x 79.0 mm, 49 parts (0 on the bottom side), 37 nets.

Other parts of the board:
FID1, FID2, FID3: Fiducial_1mm_Mask2mm

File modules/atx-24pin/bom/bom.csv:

Reference,Qty,Value,Footprint,MPN,Manufacturer,LCSC,LC_Stock,Chosen_Distributor,Datasheet,Validated,DNP,Notes
"C1,C2",2,1uF,0603,,,,,,,,,
C8,1,1µF,0805,,,,,,,,,
"C13,C11,C6,C14,C10,C3,C5,C9,C12,C4",10,100nF,0402,,,,,,,,,
"C15,C7",2,10µF,0805,,,,,,,,,
D1,1,D_Schottky,SMA,SS34,MDD,C8678,,,,,,VBUS->5VSB ORing Schottky (bench USB power). D_SMA fits 1-3A parts (e.g. SS34); pick per bench-power current.
D2,1,LED,0603,,,,,,,,,
J1,1,TO-HUB,RJ45_Amphenol_54602-x08_Horizontal,,,,,,,,,"RJ-45 8P8C shielded FTP, locking-boot, right-angle/inline; Amphenol 54602-x08 placeholder - confirm exact jack"
J2,1,TO-HUB-PWR,JST_XH_S2B-XH-A_1x02_P2.50mm_Horizontal,,,,,,,,,"2-pin +5VSB power, right-angle JST-XH (inline)"
J3,1,ATX-24 (PSU),Molex_Mini-Fit_Jr_5569-24A1_2x12_P4.20mm_Horizontal,,,,,,,,,ATX-24 PSU-side input: Molex 5569 2x12 right-angle MALE (spec 2.8); PSU female cable plugs on directly.
J4,1,ATX-24 (MB),Molex_Mini-Fit_Jr_5569-24A1_2x12_P4.20mm_Horizontal,,,,,,,,,ATX-24 MB-side output: Molex 5569 2x12 right-angle MALE (spec 2.8); needs F-to-F bridging cable to motherboard (CEC SKU).
J5,1,USB_C_Receptacle_USB2.0_16P,USB_C_Receptacle_XKB_U262-16XN-4BVC11,,,,,,https://www.usb.org/sites/default/files/documents/usb_type-c.zip,,,Right-angle (90deg) USB 2.0 Type-C debug port.
R1,1,R_ID (OQ-6),0402,,,,,,,,,DETECT module-ID precision resistor; value pending OQ-6
R2,1,10kΩ,0402,,,,,,,,,
"R4,R3",2,2.2kΩ,0402,,,,,,,,,
"R6,R5",2,5.1kΩ,0402,,,,,,,,,
"R10,R7,R9",3,1kΩ,0402,,,,,,,,,
"RS5,RS2,RS1",3,R002,2512,CSS2H-2512K-2L00F,Bourns,C1729157,,,,,,"Bourns CSS2H-2512K-2L00F 2mOhm 1%, 2-terminal. Honest 2-pad R_2512 land; draw the Kelvin sense taps off the terminal copper in layout."
RS6,1,R025,2512,,Vishay,,,,,,,5VSB shunt: Vishay WSK2512 25mOhm 4-terminal.
"SW2,SW1",2,SW_Push,Panasonic_EVQPUJ_EVQPUA,,,,,,,,,
U1,1,ESP32-S3-MINI-1-N4R2,ESP32-S2-MINI-1_NoAntKeepout,ESP32-S3-MINI-1-N4R2,Espressif Systems,C3013941,,,,,,ESP32-S3-MINI-1 uses the S2-MINI-1 footprint (mechanically identical)
U2,1,TJA1462A,SOIC-8_3.9x4.9mm_P1.27mm,TJA1462AT/0Z,NXP Semiconductors,C3234095,,,,,,
U3,1,LP5907MFX-3.3,SOT-23-5,LP5907MFX-3.3/NOPB,Texas Instruments,C80670,,,,,,
"U4,U5",2,74LVC1G17,SOT-23-5,SN74LVC1G17DBVR,Texas Instruments,C7836,,,https://www.ti.com/lit/ds/symlink/sn74lvc1g17.pdf,,,
"U12,U10,U13,U11",4,INA228,VSSOP-10_3x3mm_P0.5mm,INA228AIDGSR,Texas Instruments,C2887910,,,,,,

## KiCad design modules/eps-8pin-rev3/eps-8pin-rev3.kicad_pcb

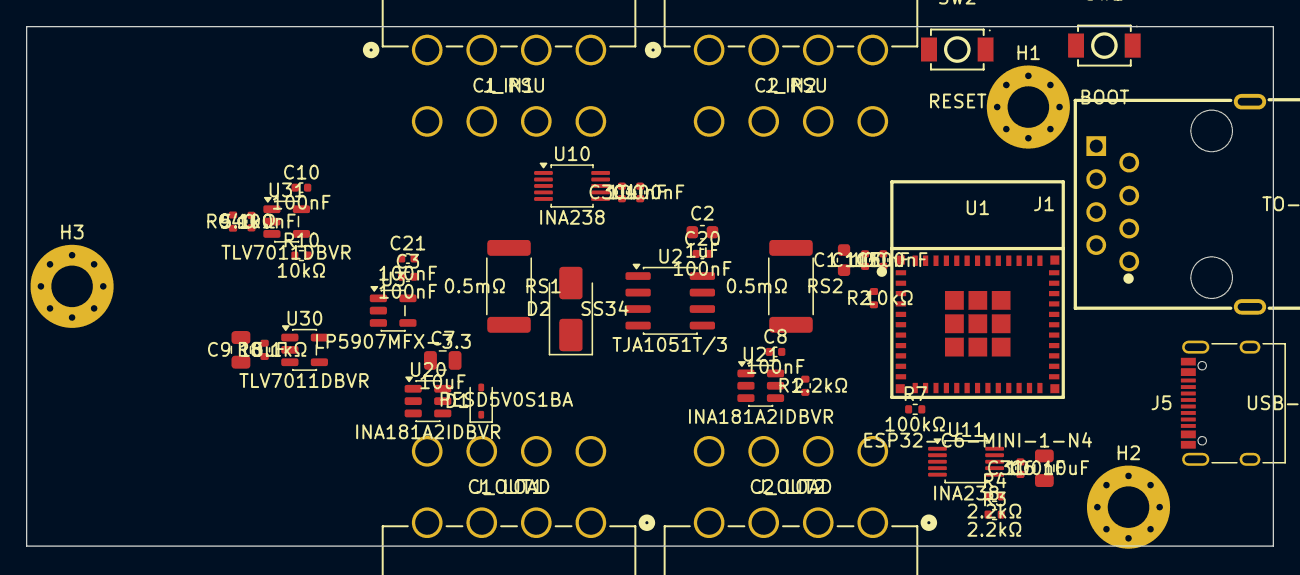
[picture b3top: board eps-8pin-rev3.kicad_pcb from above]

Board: 4 copper layers, 96.0 x 40.0 mm, 48 parts (0 on the bottom side), 28 nets, no tracks yet.

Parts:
C1, C2: 1uF; C_0603_1608Metric
C3, C4, C5, C8, C10, C11, C20, C21, C30, C31, C40: 100nF; C_0402_1005Metric
C6, C7, C9: 10uF; C_0805_2012Metric
D1: PESD5V0S1BA; D_SOD-323
D2: SS34; D_SMA
H1, H2, H3: MountingHole_3.2mm_M3_Pad_Via
J1: TO-HUB; RJ45_FTP_Shielded_Horizontal
J5: USB-C 2.0; USB_C_Receptacle_XKB_U262-16XN-4BVC11
J_IN1: C1 PSU; Molex_Mini-Fit_Jr_87427-0802_2x04_P4.20mm_RA
J_IN2: C2 PSU; Molex_Mini-Fit_Jr_87427-0802_2x04_P4.20mm_RA
J_OUT1: C1 LOAD; Molex_Mini-Fit_Jr_87427-0802_2x04_P4.20mm_RA
J_OUT2: C2 LOAD; Molex_Mini-Fit_Jr_87427-0802_2x04_P4.20mm_RA
R1, R3, R4: 2.2kΩ; R_0402_1005Metric
R2, R10: 10kΩ; R_0402_1005Metric
R7: 100kΩ; R_0402_1005Metric
R8, R9: 5.1kΩ; R_0402_1005Metric
RS1, RS2: 0.5mΩ; R_2512_6332Metric
SW1: BOOT; TS-1088-AR02016
SW2: RESET; TS-1088-AR02016
U1: ESP32-C6-MINI-1-N4; ESP32-C6-MINI-1
U2: TJA1051T/3; SOIC-8_3.9x4.9mm_P1.27mm
U3: LP5907MFX-3.3; SOT-23-5
U10, U11: INA238; VSSOP-10_3x3mm_P0.5mm
U20, U21: INA181A2IDBVR; SOT-23-6
U30, U31: TLV7011DBVR; SOT-23-5

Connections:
+3V3: C2.1, C3.1, C7.1, C8.1, C10.1, C11.1, C20.1, C21.1, C30.1, C31.1, R2.1, R3.2, R4.2, U1.3, U2.5, U3.5, U10.6, U11.2, U11.6, U20.6, U21.6, U30.5, U31.5
+5VSB: C1.1, C4.1, C6.1, D2.1, J1.1, U2.3, U3.1, U3.3
/CAN_H: J1.3, U2.7
/CAN_L: J1.6, U2.6
/CAN_RX: U1.27, U2.4
/CAN_TX: U1.26, U2.1
/DETAMPC1: U20.1, U30.3
/DETAMPC2: U21.1, U31.3
/DETC1: U1.28, U30.1
/DETC2: U1.29, U31.1
/DETECT: D1.1, J1.8, R1.1, R7.1
/DETECT_SENSE: R7.2, U1.12
/EN: C5.1, R2.2, SW2.2, U1.8
/GPIO0: SW1.2, U1.23
/I2C_SCL: R4.1, U1.25, U10.5, U11.5
/I2C_SDA: R3.1, U1.24, U10.4, U11.4
/SENSEC1_HI: J_IN1.5, J_IN1.6, J_IN1.7, J_IN1.8, RS1.1, U10.10, U20.3
/SENSEC1_LO: J_OUT1.5, J_OUT1.6, J_OUT1.7, J_OUT1.8, RS1.2, U10.8, U10.9, U20.4
/SENSEC2_HI: J_IN2.5, J_IN2.6, J_IN2.7, J_IN2.8, RS2.1, U11.10, U21.3
/SENSEC2_LO: J_OUT2.5, J_OUT2.6, J_OUT2.7, J_OUT2.8, RS2.2, U11.8, U11.9, U21.4
/THRESH: C40.1, R10.2, U30.4, U31.4
/THRESH_PWM: R10.1, U1.19
/USB_CC1: J5.A5, R8.1
/USB_CC2: J5.B5, R9.1
/USB_D_N: J5.A7, J5.B7, U1.17
/USB_D_P: J5.A6, J5.B6, U1.18
/VBUS: C9.1, D2.2, J5.A4, J5.A9, J5.B4, J5.B9
GND: C1.2, C2.2, C3.2, C4.2, C5.2, C6.2, C7.2, C8.2, C9.2, C10.2, C11.2, C20.2, C21.2, C30.2, C31.2, C40.2, D1.2, H1.1, H2.1, H3.1, J1.2, J1.SH1, J1.SH2, J5.A1, J5.A12, J5.B1, J5.B12, J5.S1, J_IN1.1, J_IN1.2, J_IN1.3, J_IN1.4, J_IN2.1, J_IN2.2, J_IN2.3, J_IN2.4, J_OUT1.1, J_OUT1.2, J_OUT1.3, J_OUT1.4, J_OUT2.1, J_OUT2.2, J_OUT2.3, J_OUT2.4, R1.2, R8.2, R9.2, SW1.1, SW2.1, U1.1, U1.2, U1.11, U1.14, U1.36, U1.37, U1.38, U1.39, U1.40, U1.41, U1.42, U1.43, U1.44, U1.45, U1.46, U1.47, U1.48, U1.49, U1.50, U1.51, U1.52, U1.53, U2.2, U2.8, U3.2, U10.1, U10.2, U10.7, U11.1, U11.7, U20.2, U20.5, U21.2, U21.5, U30.2, U31.2

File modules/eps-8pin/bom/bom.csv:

Reference,Qty,Value,Footprint,MPN,Manufacturer,LCSC,DNP,Notes
"C1,C2",2,1uF,C_0603_1608Metric,CL10B105KO8NNNC,Samsung,C15849,,
"C3,C4,C5,C8,C10,C11",6,100nF,C_0402_1005Metric,CL05B104KO5NNNC,Samsung,C1525,,
"C6,C7,C9",3,10uF,C_0805_2012Metric,CL21A106KAYNNNE,Samsung,C15850,,
D1,1,PESD5V0S1BA,D_SOD-323,PESD5V0S1BA,Nexperia,C5261083,,
D2,1,SS34,D_SMA,SS34,MDD,C8678,,
J1,1,TO-HUB,RJ45_Amphenol_54602-x08_Horizontal,54602-908LF,Amphenol,C2847314,,
J5,1,USB-C 2.0,USB_C_Receptacle_XKB_U262-16XN-4BVC11,U262-16XN-4BVC11,XKB,C2765186,,
J_IN1,1,C1 PSU,Molex_Mini-Fit_Jr_5569-08A2_2x04_P4.20mm_Horizontal,,,,,THT power connector — hand-solder/consign
J_IN2,1,C2 PSU,Molex_Mini-Fit_Jr_5569-08A2_2x04_P4.20mm_Horizontal,,,,,THT power connector — hand-solder/consign
J_OUT1,1,C1 LOAD,Molex_Mini-Fit_Jr_5569-08A2_2x04_P4.20mm_Horizontal,,,,,THT power connector — hand-solder/consign
J_OUT2,1,C2 LOAD,Molex_Mini-Fit_Jr_5569-08A2_2x04_P4.20mm_Horizontal,,,,,THT power connector — hand-solder/consign
"R1,R3,R4",3,2.2kΩ,R_0402_1005Metric,0402WGF2201TCE,UNI-ROYAL,C25879,,
R2,1,10kΩ,R_0402_1005Metric,0402WGF1002TCE,UNI-ROYAL,C25744,,
R7,1,100kΩ,R_0402_1005Metric,0402WGF1003TCE,UNI-ROYAL,C25741,,
"R8,R9",2,5.1kΩ,R_0402_1005Metric,0402WGF5101TCE,UNI-ROYAL,C25905,,
"RS1,RS2",2,0.5mΩ,R_2512_6332Metric,,,,,OQ-11 shunt — pick 0.5mΩ 2512 part
SW1,1,BOOT,TS-1088-AR02016,TS-1088-AR02016,XKB,C720477,,
SW2,1,RESET,TS-1088-AR02016,TS-1088-AR02016,XKB,C720477,,
U1,1,ESP32-S3-MINI-1-N4R2,ESP32-S2-MINI-1_NoAntKeepout,ESP32-S3-MINI-1-N4R2,Espressif Systems,C3013941,,
U2,1,TJA1051T/3,SOIC-8_3.9x4.9mm_P1.27mm,TJA1051T/3,NXP,C38695,,
U3,1,LP5907MFX-3.3,SOT-23-5,LP5907MFX-3.3,Texas Instruments,C80670,,
"U10,U11",2,INA238,VSSOP-10_3x3mm_P0.5mm,INA238AIDGSR,Texas Instruments,C2868250,,
